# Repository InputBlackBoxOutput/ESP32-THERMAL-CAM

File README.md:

# ESP32 THERMAL CAM

## Assembly
- Enclosure consists of two parts and is held together using self-tapping screws 
- The PCB is attached to the enclosure using self-tapping screws driven into mounting bosses

## Hardware block diagram
- ESP32-WROOM: Control the functionality of the entire design
- LEDs: Indicate the status of the thermal camera
- Pushbutton: Indicate the camera to save the image
- TFT Display: Display thermal images captured by the camera
- SD Card: Store thermal image captured by the camera
- TOF Proximity Sensor: Calculate the proximity of the camera with the surface in front of it
- IR Thermal Sensor Array: Capture IR emissions and create a thermal image of the surface
- LiPo Battery + BMS: Provide power to the camera thereby making it portable

## Application
- Connect with the thermal camera
- Display thermal image with an appropriate legend 
- Capture and save the thermal image 

### Made with lots of ⏱️, 📚 and ☕ by InputBlackBoxOutput

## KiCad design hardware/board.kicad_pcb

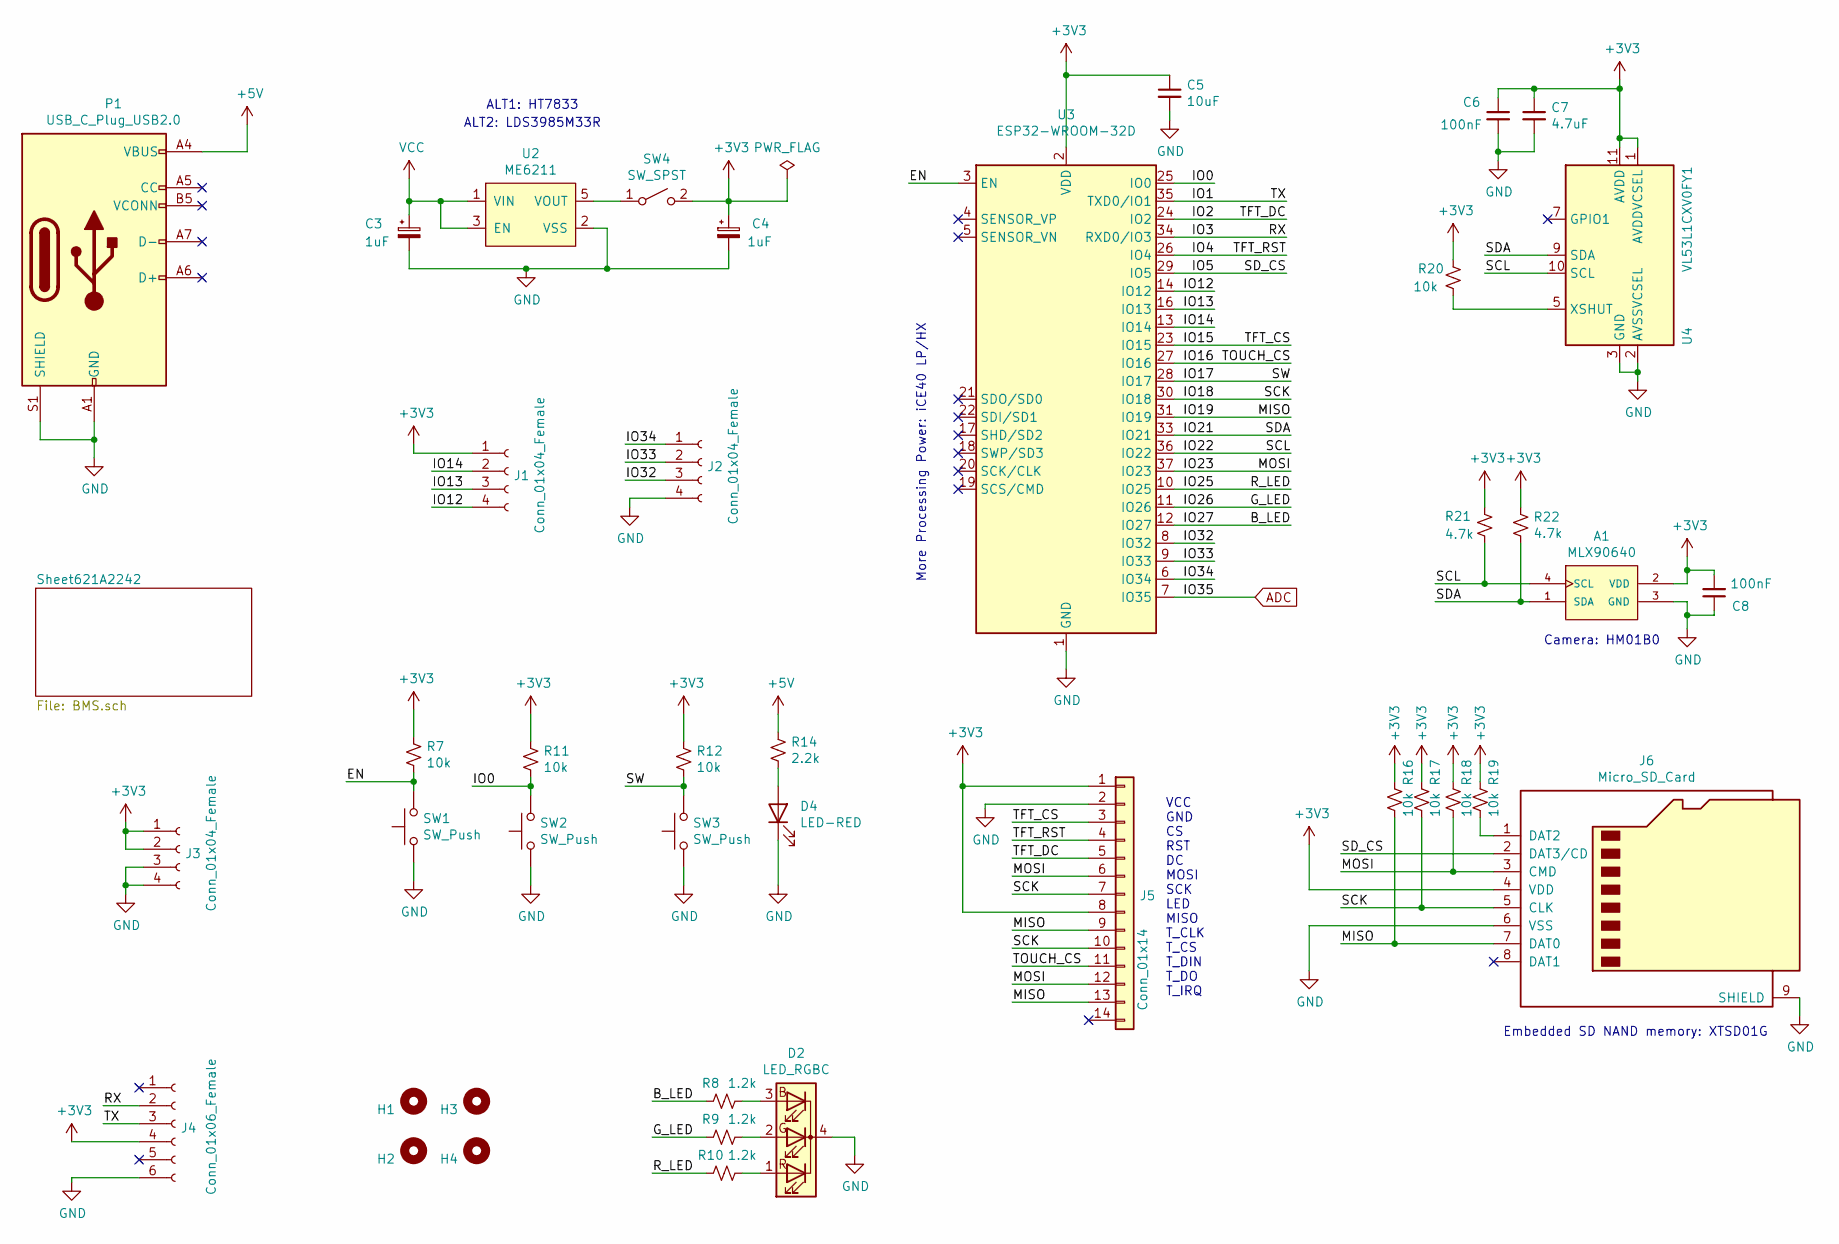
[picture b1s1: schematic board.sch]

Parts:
A1: MLX90640; TO292P930H600-4; PARTREV 11
C3, C4: 1uF; C_0805_2012Metric_Pad1.18x1.45mm_HandSolder
C5: 10uF; C_0805_2012Metric_Pad1.18x1.45mm_HandSolder
C6, C8: 100nF; C_0805_2012Metric_Pad1.18x1.45mm_HandSolder
C7: 4.7uF; C_0805_2012Metric_Pad1.18x1.45mm_HandSolder
D2: LED_RGBC; LED_D5.0mm-4_RGB
D4: LED-RED; LED_0805_2012Metric_Pad1.15x1.40mm_HandSolder
H1, H2, H3, H4: MountingHole; MountingHole_2.2mm_M2
J1, J2, J3: Conn_01x04_Female; PinSocket_1x04_P2.54mm_Vertical
J4: Conn_01x06_Female; PinSocket_1x06_P2.54mm_Vertical
J5: Conn_01x14; PinSocket_1x14_P2.54mm_Vertical_SMD_Pin1Left
J6: Micro_SD_Card; GCT-MEM2055-00-190-01-A
P1: USB_C_Plug_USB2.0; USB_C_Receptacle_HRO_TYPE-C-31-M-12
R7, R11, R12, R16, R17, R18, R19, R20: 10k; R_0805_2012Metric_Pad1.20x1.40mm_HandSolder
R8, R9, R10: 1.2k; R_0805_2012Metric_Pad1.20x1.40mm_HandSolder
R14: 2.2k; R_0805_2012Metric_Pad1.20x1.40mm_HandSolder
R21, R22: 4.7k; R_0805_2012Metric_Pad1.20x1.40mm_HandSolder
SW1, SW2: SW_Push; SW_SPST_Omron_B3FS-100xP
SW3: SW_Push; SW_SPST_EVQP7A
SW4: SW_SPST; SW_SPDT_PCM12
U2: ME6211; SOT-23-5_HandSoldering
U3: ESP32-WROOM-32D; ESP32-WROOM-32
U4: VL53L1CXV0FY1; ST_VL53L1x

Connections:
+3V3: A1.2 (VDD), C4.1, C5.1, C6.1, C7.1, C8.2, J1.1, J3.1, J3.2, J4.4, J5.1, J5.8, J6.4 (VDD), R7.1, R11.1, R12.1, R16.1, R17.1, R18.1, R19.1, R20.1, R21.1, R22.1, SW4.2 (B), U3.2 (VDD), U4.1 (AVDDVCSEL), U4.11 (AVDD)
+5V: P1.A4 (VBUS), P1.A9 (VBUS), P1.B4 (VBUS), P1.B9 (VBUS), R14.1; also elsewhere on the board
/B_LED: R8.2, U3.12 (IO27)
/EN: R7.2, SW1.2, U3.3 (EN)
/G_LED: R9.2, U3.11 (IO26)
/IO0: R11.2, SW2.2, U3.25 (IO0)
/IO1: J4.3, U3.35 (TXD0/IO1)
/IO2: J5.5, U3.24 (IO2)
/IO3: J4.2, U3.34 (RXD0/IO3)
/IO4: J5.4, U3.26 (IO4)
/IO5: J6.2 (DAT3/CD), U3.29 (IO5)
/IO12: J1.4, U3.14 (IO12)
/IO13: J1.3, U3.16 (IO13)
/IO14: J1.2, U3.13 (IO14)
/IO15: J5.3, U3.23 (IO15)
/IO16: J5.11, U3.27 (IO16)
/IO17: R12.2, SW3.2, U3.28 (IO17)
/IO18: J5.7, J5.10, J6.5 (CLK), R17.2, U3.30 (IO18)
/IO19: J5.9, J5.13, J6.7 (DAT0), R16.2, U3.31 (IO19)
/IO21: A1.1 (SDA), R22.2, U3.33 (IO21), U4.9 (SDA)
/IO22: A1.4 (SCL), R21.2, U3.36 (IO22), U4.10 (SCL)
/IO23: J5.6, J5.12, J6.3 (CMD), R18.2, U3.37 (IO23)
/IO25: R10.2, U3.10 (IO25)
/IO32: J2.3, U3.8 (IO32)
/IO33: J2.2, U3.9 (IO33)
/IO34: J2.1, U3.6 (IO34)
ADC: U3.7 (IO35); also elsewhere on the board
GND: A1.3 (GND), C3.2, C4.2, C5.2, C6.2, C7.2, C8.1, D2.4 (K), D4.1 (K), J2.4, J3.3, J3.4, J4.6, J5.2, J6.6 (VSS), J6.9 (SHIELD), P1.A1 (GND), P1.A12 (GND), P1.B1 (GND), P1.B12 (GND), P1.S1 (SHIELD), SW1.1, SW2.1, SW3.1, U2.2 (VSS), U3.1 (GND), U3.15 (GND), U3.38 (GND), U3.39 (GND), U4.2 (AVSSVCSEL), U4.3 (GND), U4.4 (GND), U4.6 (GND), U4.12 (GND); also elsewhere on the board
unnamed: D2.1 (RA), R10.1
unnamed: D2.2 (GA), R9.1
unnamed: D2.3 (BA), R8.1
unnamed: D4.2 (A), R14.2
unnamed: J6.1 (DAT2), R19.2
unnamed: R20.2, U4.5 (XSHUT)
unnamed: SW4.1 (A), U2.5 (VOUT)
VCC: C3.1, U2.1 (VIN), U2.3 (EN); also elsewhere on the board

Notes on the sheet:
Camera: HM01B0
More Processing Power: iCE40 LP/HX
VCC GND CS RST DC MOSI SCK LED MISO T_CLK T_CS T_DIN T_DO T_IRQ
Embedded SD NAND memory: XTSD01G
ALT1: HT7833
ALT2: LDS3985M33R

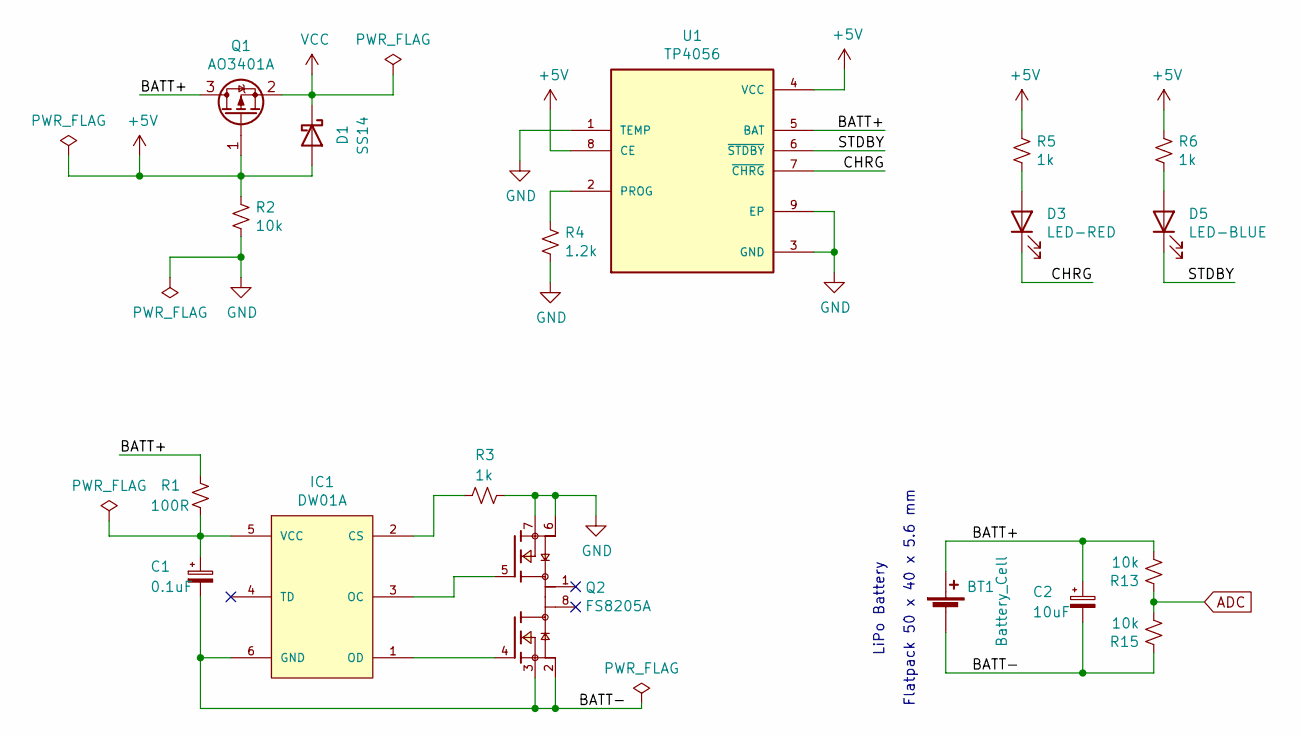
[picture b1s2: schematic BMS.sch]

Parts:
BT1: Battery_Cell; SolderWire-01x02-SMD-BATT
C1: 0.1uF; C_0805_2012Metric_Pad1.18x1.45mm_HandSolder
C2: 10uF; C_0805_2012Metric_Pad1.18x1.45mm_HandSolder
D1: SS14; D_SMB
D3: LED-RED; LED_0805_2012Metric_Pad1.15x1.40mm_HandSolder
D5: LED-BLUE; LED_0805_2012Metric_Pad1.15x1.40mm_HandSolder
IC1: DW01A; SOT-23-6_Handsoldering; MPN DW01A; LCSC C351410
Q1: AO3401A; SOT-23
Q2: FS8205A; SOP65P640X120-8N; PARTREV 1.7
R1: 100R; R_0805_2012Metric_Pad1.20x1.40mm_HandSolder
R2, R13, R15: 10k; R_0805_2012Metric_Pad1.20x1.40mm_HandSolder
R3, R5, R6: 1k; R_0805_2012Metric_Pad1.20x1.40mm_HandSolder
R4: 1.2k; R_0805_2012Metric_Pad1.20x1.40mm_HandSolder
U1: TP4056; SOP127P600X175-9N

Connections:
+5V: D1.2 (A), Q1.1 (G), R2.1, R5.1, R6.1, U1.4 (VCC), U1.8 (CE); also elsewhere on the board
/Sheet621A2242/BATT+: BT1.1 (+), C2.1, Q1.3 (D), R1.1, R13.2, U1.5 (BAT)
/Sheet621A2242/BATT-: BT1.2 (-), C1.2, C2.2, IC1.6 (GND), Q2.2, Q2.3, R15.1
/Sheet621A2242/CHRG: D3.1 (K), U1.7 (~CHRG)
/Sheet621A2242/STDBY: D5.1 (K), U1.6 (~STDBY)
ADC: R13.1, R15.2; also elsewhere on the board
GND: Q2.6, Q2.7, R2.2, R3.1, R4.2, U1.1 (TEMP), U1.3 (GND), U1.9 (EP); also elsewhere on the board
unnamed: C1.1, IC1.5 (VCC), R1.2
unnamed: D3.2 (A), R5.2
unnamed: D5.2 (A), R6.2
unnamed: IC1.1 (OD), Q2.4
unnamed: IC1.2 (CS), R3.2
unnamed: IC1.3 (OC), Q2.5
unnamed: R4.1, U1.2 (PROG)
VCC: D1.1 (K), Q1.2 (S); also elsewhere on the board

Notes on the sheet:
LiPo Battery
Flatpack 50 x 40 x 5.6 mm

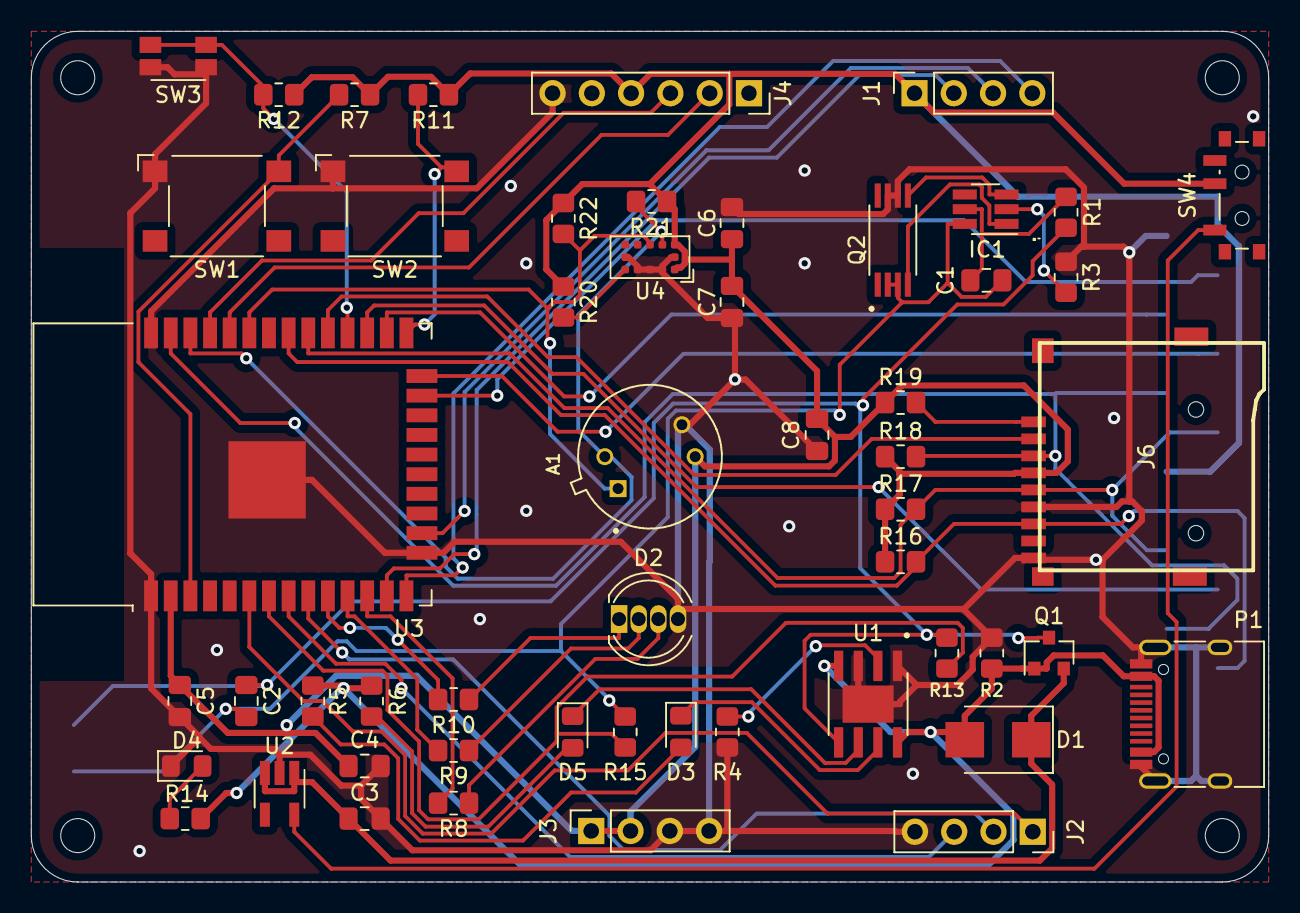
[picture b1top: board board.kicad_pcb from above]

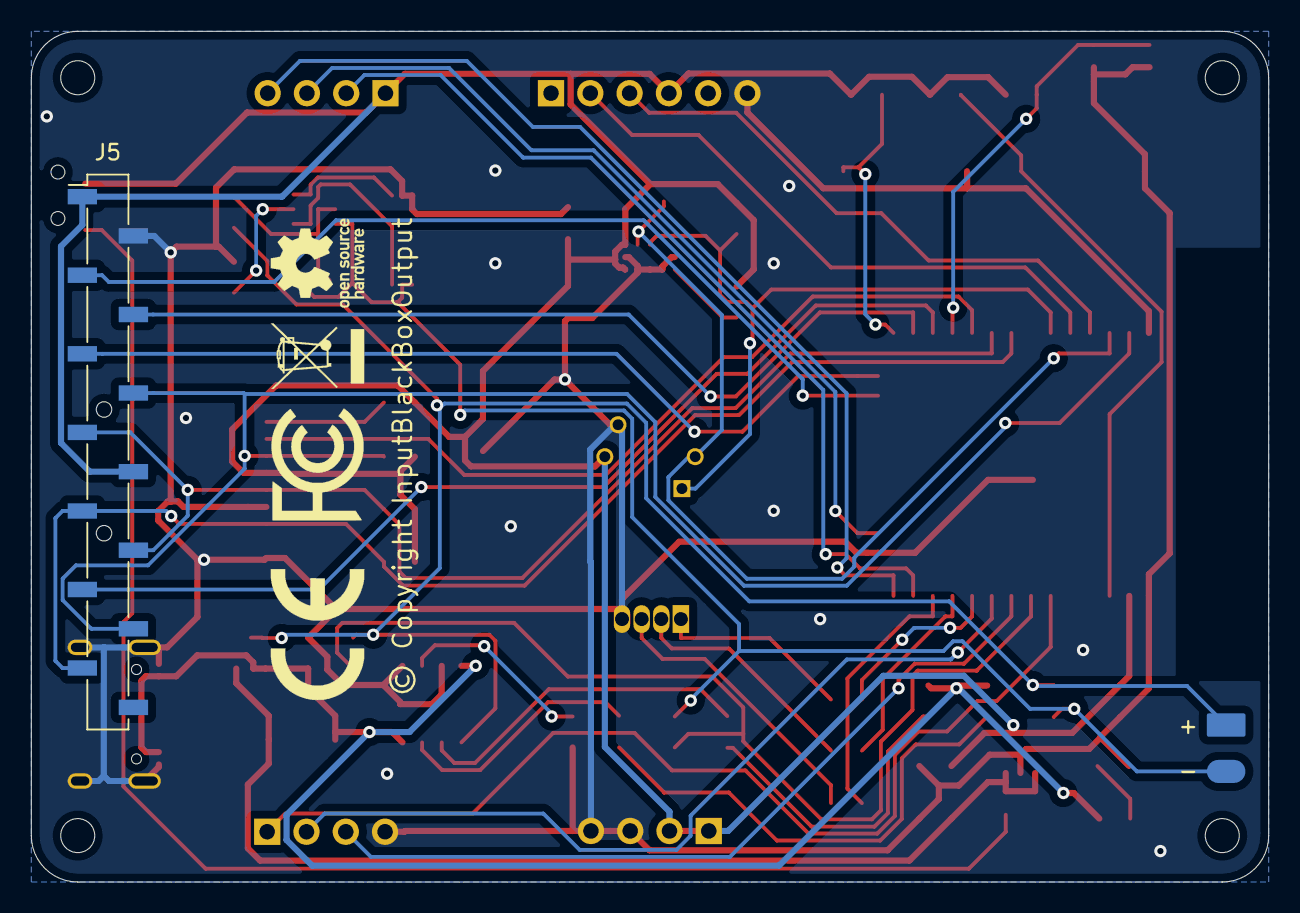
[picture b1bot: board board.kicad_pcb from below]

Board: 2 copper layers, 80.0 x 55.0 mm, 59 parts (2 on the bottom side), 47 nets.

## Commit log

2022-02-27 Hardware added
2022-02-27 Enclosure added
2022-03-02 Silkscreen markings added + Minor changes to tracks
2022-03-03 Firmware: MLX90640 code added
2022-03-03 Firmware: WiFi Server code added
2022-03-10 Minor changes to the PCB
2022-04-17 README: Exploded view image added
2022-04-18 Enclosure lid variants added
2022-05-01 Documents added
2022-05-01 README: Hardware block diagram image added
2022-05-03 Windows application files added
2022-05-05 CE, FCC, WEEE and OSHW markings added to PCB
2022-05-18 Electron application UI
2022-05-27 Electron application: WiFi connection
2022-05-27 Electron application: Generic modal
2022-06-23 Electron application: Files added
2022-06-25 Electron application: Help & About
2022-06-25 Electron application: Minor changes
2022-07-04 Folder reorganized: hardware
2022-07-31 README: Interface screenshot added
2023-10-04 README: Info added
2025-08-27 README: Minor changes

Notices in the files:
hardware/board.kicad_pcb:
© Copyright InputBlackBoxOutput
